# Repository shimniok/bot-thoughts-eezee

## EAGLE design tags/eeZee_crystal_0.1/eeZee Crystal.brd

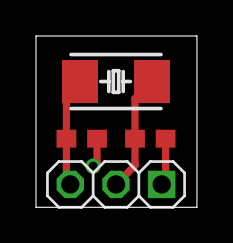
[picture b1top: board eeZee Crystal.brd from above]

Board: 2 copper layers, 8.9 x 9.5 mm, 4 parts (0 on the bottom side), 3 nets.

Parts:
C1, C2: 8pF; C0603
JP1: XTAL; 1X03-S
Q1: 16MHz; NDK_2PAD_5X3

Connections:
GND: C1.2, C2.2, JP1.1
unnamed: C1.1, JP1.2, Q1.P$2
unnamed: C2.1, JP1.3, Q1.P$1

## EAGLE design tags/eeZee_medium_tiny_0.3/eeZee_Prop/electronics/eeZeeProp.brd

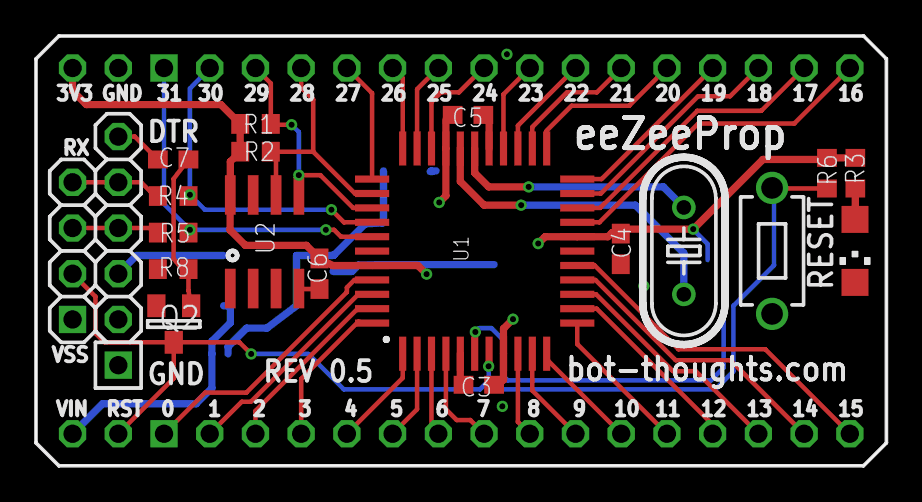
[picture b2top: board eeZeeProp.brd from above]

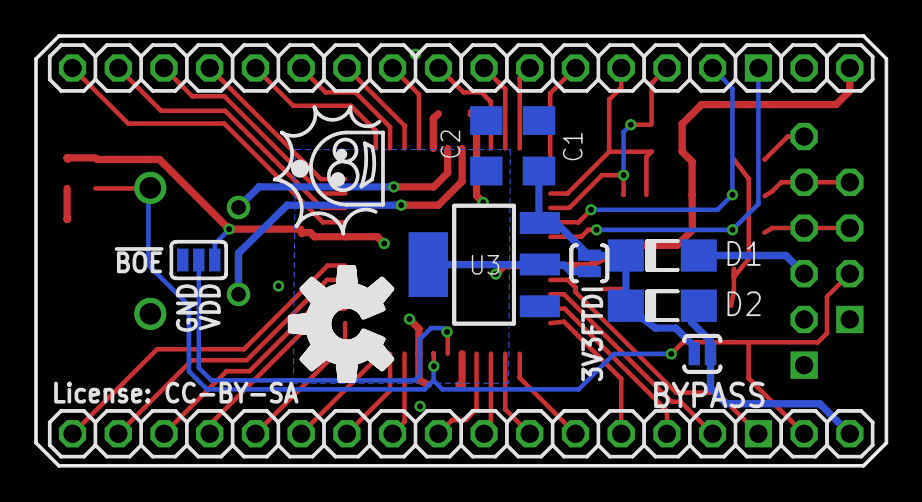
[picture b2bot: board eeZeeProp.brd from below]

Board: 2 copper layers, 47.2 x 23.9 mm, 34 parts (14 on the bottom side), 46 nets.

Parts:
C1, C2: 10uF; C1206
C3, C4, C5, C6, C7: 0.1uF; C0603
D1, D2: MBR130LSFT1; SOD123FL
JP1, JP5: 1X16-S
JP2: VIN; 1X01
JP3: PROP PLUG; 1X04-S
JP4: FTDI; 1X06-S
JP6: GND; 1X01
JP7: !RES; 1X01
JP8: 3V3; 1X01
LED1: green; CHIPLED_1206
Q1: 5MHz; HC49U-V
Q2: 2N3904SMD; SOT-23
R1, R2, R4, R5, R8: 10k; R0603
R3: 330; R0603
R6: 1k; R0603
SJ1: BYPASS; SJ_2S-NO
SJ2: !BOE; SJ_3
SJ3: 3V3FTDI; SJ_2S-NO
SW1: RESET; 6MMTACTILE_RECT
U1: P8X32A-Q44
U2: 24LC256-I/ST; SO-08
U3: NCP1117 3V3; SOT223

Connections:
!BOE: SJ2.2, U1.6
!RES: JP3.2, JP7.1, Q2.1, R6.2, SW1.P$1, U1.7
DTR: C7.2, JP4.6
GND: C1.2, C2.2, C3.2, C4.2, C5.2, C6.2, JP3.1, JP4.1, JP6.1, LED1.C, Q2.2, R8.1, SJ2.1, SW1.P$2, U1.5, U1.17, U1.27, U1.39, U2.1, U2.2, U2.3, U2.4, U2.7, U3.1
unnamed: JP5.1, U1.41
unnamed: JP5.2, U1.42
unnamed: JP5.3, U1.43
unnamed: JP5.4, U1.44
unnamed: LED1.A, R3.1
unnamed: JP5.5, U1.1
unnamed: JP5.6, U1.2
unnamed: JP5.7, U1.3
unnamed: JP5.8, U1.4
unnamed: JP5.9, U1.9
unnamed: JP5.10, U1.10
unnamed: JP5.11, U1.11
unnamed: JP5.12, U1.12
unnamed: JP5.13, U1.13
unnamed: JP5.14, U1.14
unnamed: JP5.15, U1.15
unnamed: JP5.16, U1.16
unnamed: JP1.5, U1.34
unnamed: JP1.6, U1.33
unnamed: JP1.7, U1.32
unnamed: JP1.8, U1.31
unnamed: JP1.9, U1.26
unnamed: JP1.10, U1.25
unnamed: JP1.11, U1.24
unnamed: JP1.12, U1.23
unnamed: JP1.13, U1.22
unnamed: JP1.14, U1.21
unnamed: JP1.15, U1.20
unnamed: JP1.16, U1.19
unnamed: C7.1, Q2.3, R8.2
P28: JP1.4, R2.1, U1.35, U2.6
P29: JP1.3, R1.1, U1.36, U2.5
P30: JP1.2, R4.2, U1.37
P31: JP1.1, R5.2, U1.38
RXI: JP3.4, JP4.5, R4.1
TXO: JP3.3, JP4.4, R5.1
V+: C1.1, D1.C, D2.C, SJ1.2, SJ3.2, U3.3
VDD: C2.1, C3.1, C4.1, C5.1, C6.1, JP8.1, R1.2, R2.2, R3.2, R6.1, SJ2.3, SJ3.1, U1.8, U1.18, U1.30, U1.40, U2.8, U3.2, U3.4
VIN: D2.A, JP2.1, SJ1.1
VUSB: D1.A, JP4.3
XI: Q1.2, U1.28
XO: Q1.1, U1.29

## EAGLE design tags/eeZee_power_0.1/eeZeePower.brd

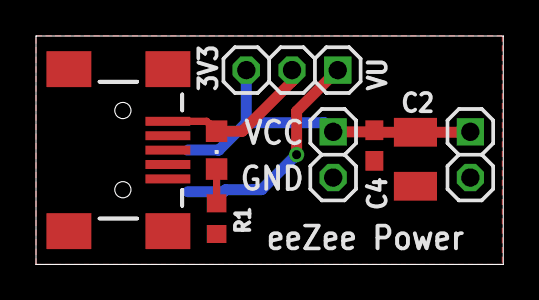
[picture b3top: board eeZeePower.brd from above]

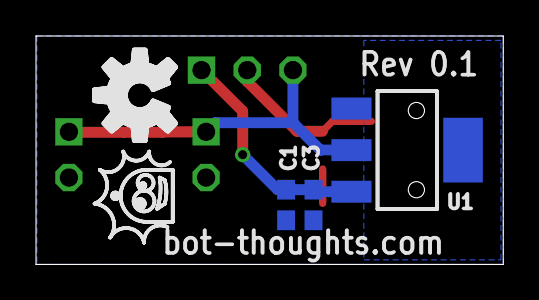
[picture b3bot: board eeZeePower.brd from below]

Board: 2 copper layers, 26.0 x 12.7 mm, 11 parts (3 on the bottom side), 5 nets.

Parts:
C1, C4: 0.1uF; C0603
C2: 100uF; SMC_B
C3: 10uF; C0603
JP1: USBSMD; USB-MINIB
JP3, JP4: 1X02-S
JP10: SEL; 1X03-S
LED1: CHIPLED_0805
R1: R0603
U1: SOT223

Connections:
GND: C1.2, C2.-, C3.2, C4.2, JP1.GND, JP3.2, JP4.2, R1.1, U1.1
unnamed: LED1.C, R1.2
VBUS: JP1.VBUS, JP10.2, LED1.A
VIN: C1.1, C3.1, JP10.1, U1.3
VOUT: C2.+, C4.1, JP3.1, JP4.1, JP10.3, U1.2

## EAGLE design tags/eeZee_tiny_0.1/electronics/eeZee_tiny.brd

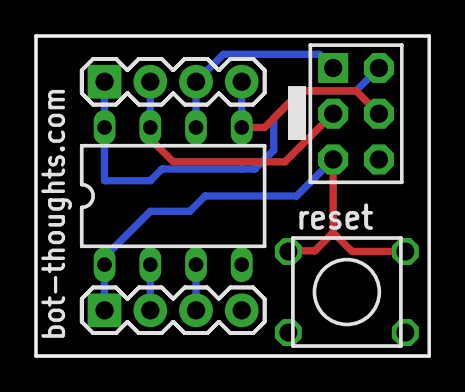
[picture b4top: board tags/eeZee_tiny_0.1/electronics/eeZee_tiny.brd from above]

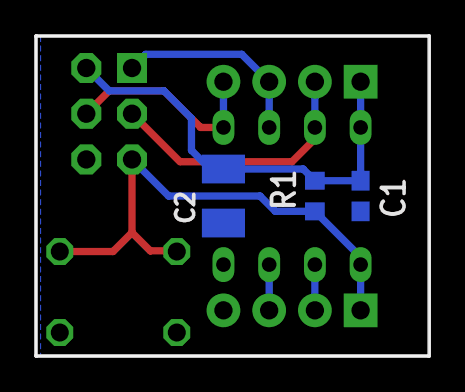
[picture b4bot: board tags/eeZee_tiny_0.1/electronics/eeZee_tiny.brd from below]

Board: 2 copper layers, 21.8 x 17.8 mm, 8 parts (3 on the bottom side), 8 nets.

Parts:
C1: 0.1uF; C0603
C2: 100uF; SMC_B
IC1: attiny; DIL08
J2: avrisp; CON6P2R
JP1, JP2: 1X04
R1: 10k; R0603
S2: reset; 6MMTACTILE_4PIN

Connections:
!RESET: IC1.1, J2.5, JP1.1, R1.1, S2.B1, S2.B2
GND: C1.2, C2.-, IC1.4, J2.6, JP1.4, S2.A1, S2.A2
MISO: IC1.6, J2.1, JP2.3
MOSI: IC1.5, J2.4, JP2.4
unnamed: IC1.2, JP1.2
unnamed: IC1.3, JP1.3
SCK: IC1.7, J2.3, JP2.2
VCC: C1.1, C2.+, IC1.8, J2.2, JP2.1, R1.2

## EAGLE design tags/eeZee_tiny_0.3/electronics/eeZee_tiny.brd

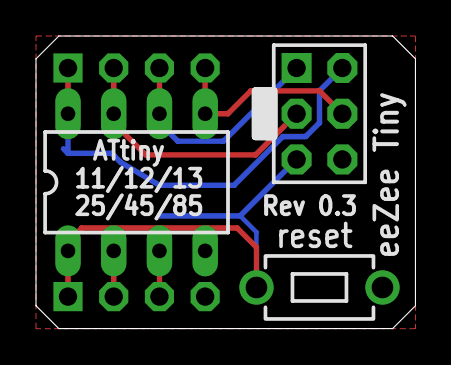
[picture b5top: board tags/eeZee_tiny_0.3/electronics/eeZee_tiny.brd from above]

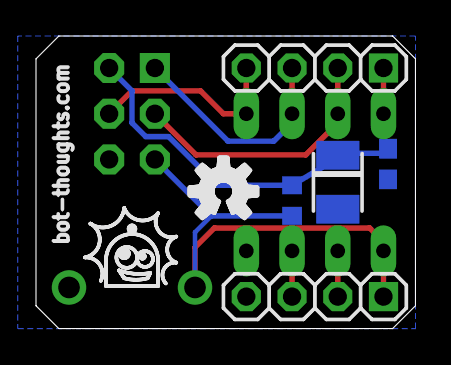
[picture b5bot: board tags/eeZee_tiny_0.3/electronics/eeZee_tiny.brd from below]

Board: 2 copper layers, 21.1 x 16.3 mm, 8 parts (5 on the bottom side), 8 nets.

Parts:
C1: 0.1uF; C0603
C2: 100uF; SMC_B
IC1: ATtiny; DIL08
J2: avrisp; CON6P2R
JP3, JP4: 1X04-S
R1: 10k; R0603
S1: reset; 6MMTACTILE_RECT

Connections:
!RESET: IC1.1, J2.5, JP3.1, R1.1, S1.P$1
GND: C1.2, C2.-, IC1.4, J2.6, JP3.4, S1.P$2
MISO: IC1.6, J2.1, JP4.3
MOSI: IC1.5, J2.4, JP4.4
unnamed: IC1.2, JP3.2
unnamed: IC1.3, JP3.3
SCK: IC1.7, J2.3, JP4.2
VCC: C1.1, C2.+, IC1.8, J2.2, JP4.1, R1.2

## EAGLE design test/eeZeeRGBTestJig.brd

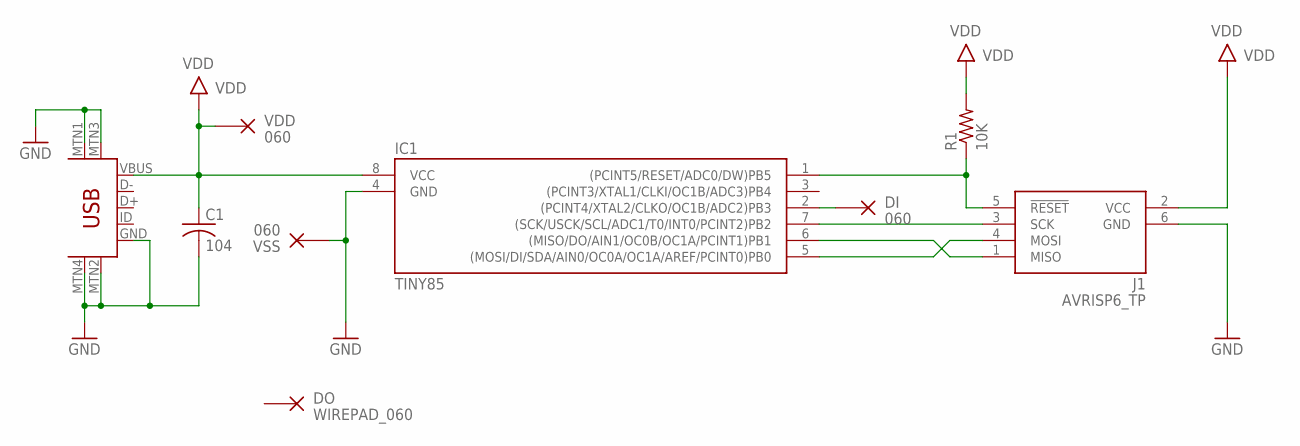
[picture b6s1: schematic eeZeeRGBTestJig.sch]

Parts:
C1: 104; C0603
DI: 060; PAD_060
DO: WIREPAD_060; PAD_060
IC1: TINY85; SOIC8N
J1: AVRISP6_TP; 2X3_TP
R1: 10K; R0603
U$1: USB-MINIB-5PIN; USB-MINIB
VDD: 060; PAD_060
VSS: 060; PAD_060

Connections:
!RESET: IC1.1 ((PCINT5/RESET/ADC0/DW)PB5), J1.5 (!RESET), R1.1
GND: C1.2, IC1.4 (GND), J1.6 (GND), U$1.GND, U$1.MTN1 (MTN2), U$1.MTN2 (MTN3), U$1.MTN3 (MTN1), U$1.MTN4, VSS.P$1
unnamed: IC1.5 ((MOSI/DI/SDA/AIN0/OC0A/OC1A/AREF/PCINT0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), J1.4 (MOSI)
unnamed: IC1.6 ((MISO/DO/AIN1/OC0B/OC1A/PCINT1)PB1), J1.1 (MISO)
unnamed: IC1.7 ((SCK/USCK/SCL/ADC1/T0/INT0/PCINT2)PB2), J1.3 (SCK)
unnamed: DI.P$1, IC1.2 ((PCINT4/XTAL2/CLKO/OC1B/ADC2)PB3)
VDD: C1.1, IC1.8 (VCC), J1.2 (VCC), R1.2, U$1.VBUS, VDD.P$1

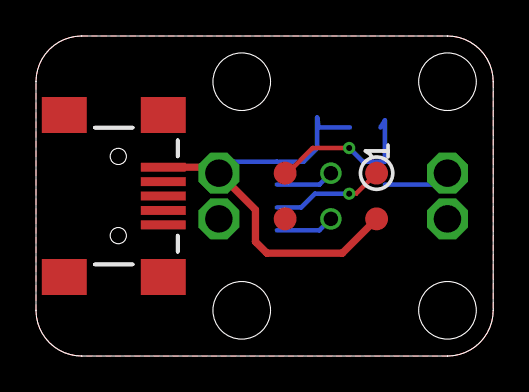
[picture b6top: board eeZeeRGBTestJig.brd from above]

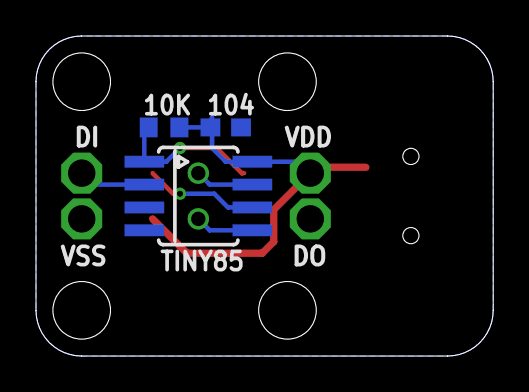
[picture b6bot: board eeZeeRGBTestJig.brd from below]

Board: 2 copper layers, 25.4 x 17.8 mm, 9 parts (7 on the bottom side), 7 nets.

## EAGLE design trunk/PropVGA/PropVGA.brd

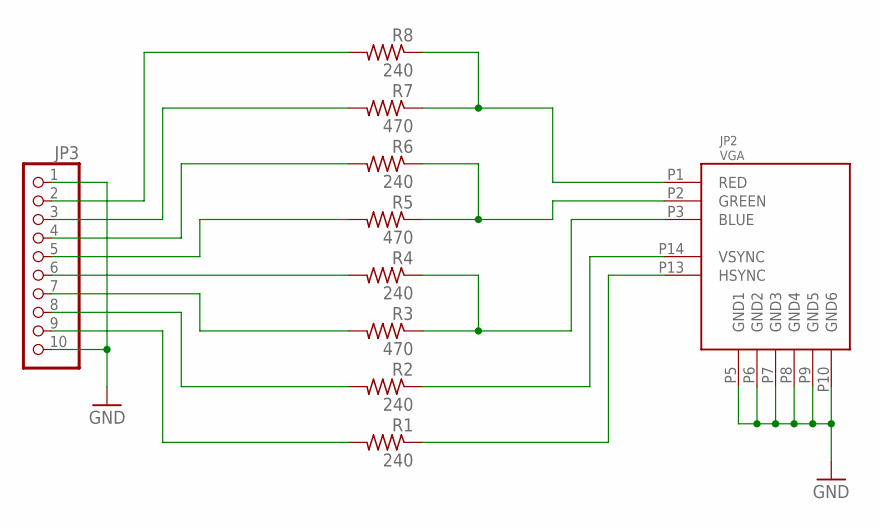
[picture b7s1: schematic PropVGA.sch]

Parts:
JP2: VGA; FCI_DSUB_HD_15_RA
JP3: PINHD-1X10_2.54-S; 1X10-S
R1, R2, R4, R6, R8: 240; 0204/5
R3, R5, R7: 470; 0204/5

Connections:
B: JP2.P3 (BLUE), R3.1, R4.1
G: JP2.P2 (GREEN), R5.1, R6.1
GND: JP2.P5 (GND1), JP2.P6 (GND2), JP2.P7 (GND3), JP2.P8 (GND4), JP2.P9 (GND5), JP2.P10 (GND6), JP3.1, JP3.10
H: JP2.P14 (VSYNC), R2.1
unnamed: JP3.9, R1.2
unnamed: JP3.8, R2.2
unnamed: JP3.7, R3.2
unnamed: JP3.6, R4.2
unnamed: JP3.5, R5.2
unnamed: JP3.4, R6.2
unnamed: JP3.3, R7.2
unnamed: JP3.2, R8.2
R: JP2.P1 (RED), R7.1, R8.1
V: JP2.P13 (HSYNC), R1.1

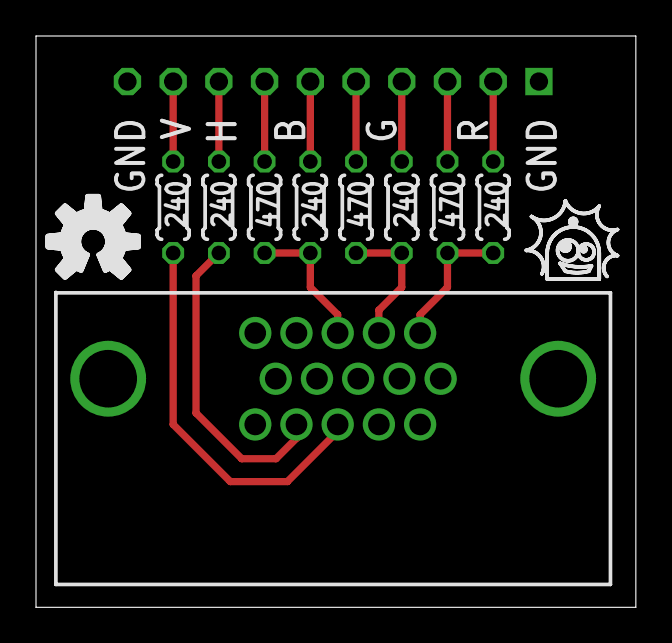
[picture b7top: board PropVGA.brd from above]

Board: 2 copper layers, 33.3 x 31.7 mm, 10 parts (1 on the bottom side), 14 nets.

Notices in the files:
tags/eeZee_medium_tiny_0.3/eeZee_Prop/electronics/eeZeeProp.brd:
License: CC-BY-SA
parts and their libraries:
SparkFun: Licensing: CC v3.0 Share-Alike You are welcome to use this library for commercial purposes.
